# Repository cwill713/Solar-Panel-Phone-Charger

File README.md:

# Solar Smartphone Charger

This is the the project, assigned by [Dr. Rob Frohne](https://github.com/frohro), that [Joshua Mularczyk](https://github.com/JoshuaMularczyk) and I designed for our Power Electronics class. This project used our knowledge of power efficiency and stepping down voltage along with our knowledge of KiCAD and LTSpice to create our own portable solar phone charges. 

## Design Objectives:
- Output 5V from a higher input voltage
- Draw 1A at the output
- Inexpensive ($20-$30 Budget)
- AS efficient as possible

## Overview

Josh and I wanted to design a solar phone charger because we thought of the potential use of people who spend a lot of time outside. We also knew that Apple products need certain specifications to charge as oppose to Andriod products so we set out to figure out how to make our charger work for both.

The first simulation/schematic of our project allowed us to get the desired outputs, but we found that it was not very efficient, so we decided to redesign our board and end up with a new string of designs

The heart of our circuit is the [LM3478](https://www.ti.com/lit/ds/symlink/lm3478.pdf?HQS=dis-dk-null-digikeymode-dsf-pf-null-wwe&ts=1654180125781&ref_url=https%253A%252F%252Fwww.ti.com%252Fgeneral%252Fdocs%252Fsuppproductinfo.tsp%253FdistId%253D10%2526gotoUrl%253Dhttps%253A%252F%252Fwww.ti.com%252Flit%252Fgpn%252Flm3478) which is a high-efficiency low-side n-channel controller. This allows us to regulate any voltage between 2.39 and 40V that could come from our 10W solar panels

## Rev 7 Design

This is the most recent KiCad schematic for our circuit design. Josh used the Texas Instrument [Webench Power Designer](https://www.ti.com/design-resources/design-tools-simulation/webench-power-designer.html) to generate this step-down circuit. The design specified a 5V to 12V input voltage based on the likely solar panel outputs. We also specified the a maximum of 1A should be be able to be drawn from our circuit.

## Rev 7 Simulation

This is the complete simulation of our circuit. We can see here that at around 7ms, the output voltage of circuit is 5V

### Voltage Outputs (5V 2.7V 2V)

This is the simulation of the voltage dividers that shows the voltage going to our USB pins. V+, D+, and D-. This will be talked about more in the testing section.

### Input and Output Current

This simulations shows us that we achieved the low input voltage that we need. The 5 Ohm resistor allowed us to simulate the current our phone would draw from the circuit. The output current of 1A will allow us to power our phone with 5W.

## Rev 7 PCB Design

This is the PCB design of the board we sourced from [JLCPCB](https://jlcpcb.com/VGS?utm_source=gg_vgs&utm_medium=cpc&gclid=Cj0KCQjwqPGUBhDwARIsANNwjV4Y9aU908uwwHsgXCAJ3L9PZ44l-hPgCvsU4kgto-ll1H0iRJroh1UaAsKwEALw_wcB),

## Rev 6 Testing

Josh and I each constructed a our own boards and tested them. When testing the boards with a 0-18V 1A power supply, we found that the boards could charge Ti-84 calculators and Andriod phones, but not an iPhone. To see if we couldn't draw enough current from the power supply, we connected our board to 24V 3A power supply and saw the same results. After we performed some research, Josh found that we needed voltage across the D+ and D- pins, 2.7 and 2V respectivly. To achieve this, we created a votalde dividers using through-hole resistors and soldered them to the back of the boards. We then tested the boards and found that we were able to succesfully charge our iPhones.

After we tested the boards in the lab, we connected our boards to our solar panels and tested them outside. We found that we were getting around 4.8V and .96A at the output which gave us 4.61W at the output. 

## Rev 6 Results
The image on the left shows the voltage being supplied to the iPhone through the 24V 4A power suplies. The image on the right shows the current being drawn by the iPhone.

More images are avaialble in the [pictures](https://github.com/cwill713/Solar-Panel-Phone-Charger/tree/main/Pictures) folder. The video of testing made by Josh is availabel [here](https://youtu.be/SS7m2UqrDPg).

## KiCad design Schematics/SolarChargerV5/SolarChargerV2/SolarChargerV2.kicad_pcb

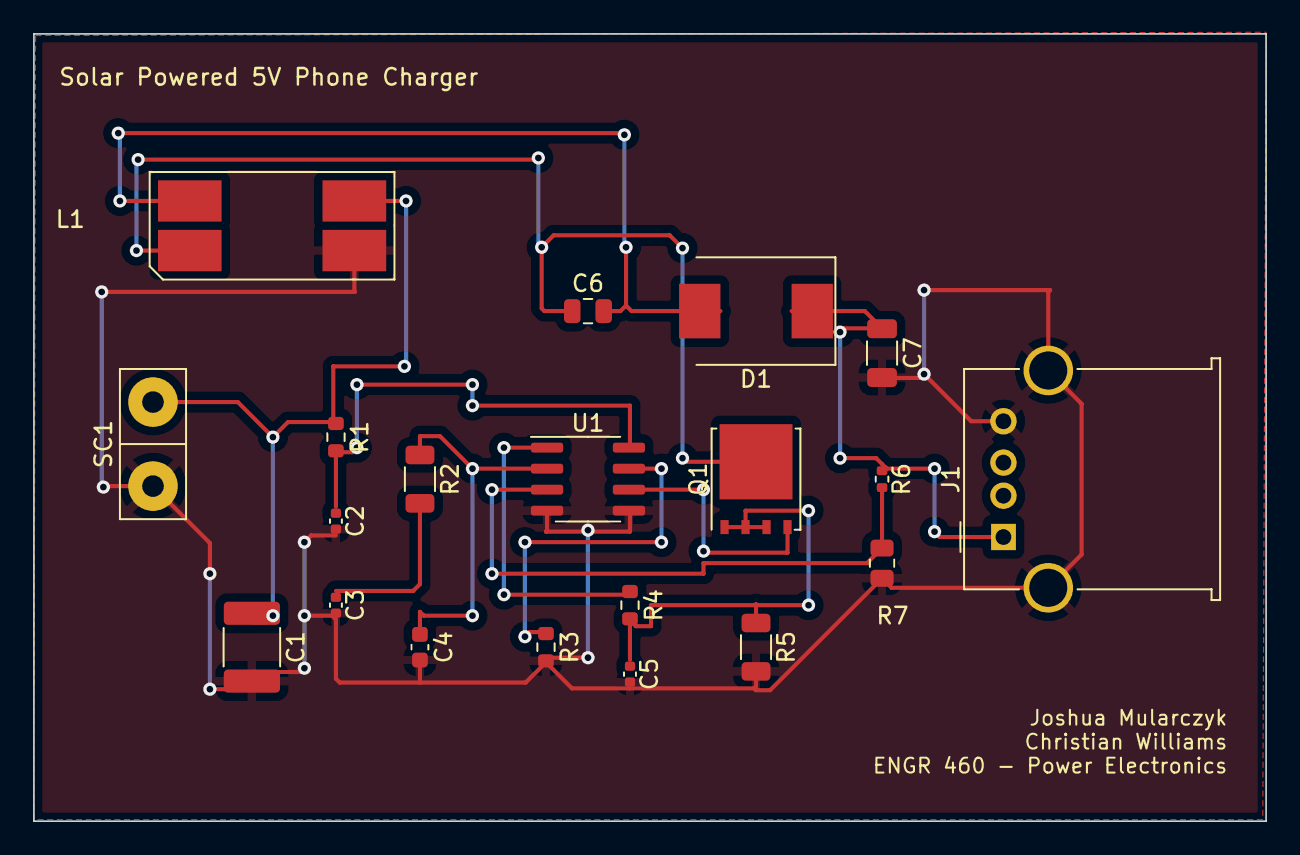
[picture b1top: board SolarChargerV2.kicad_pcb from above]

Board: 2 copper layers, 74.5 x 47.6 mm, 20 parts (0 on the bottom side), 13 nets.

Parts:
C1: 10u; C_1812_4532Metric
C2: 100n; C_0402_1005Metric
C3: 82n; C_0402_1005Metric
C4: 200p; C_0603_1608Metric
C5: 1n; C_0402_1005Metric
C6: 1u; C_0805_2012Metric
C7: 47u; C_1206_3216Metric
D1: B340; D_SMC
J1: USB_A; USB_A_Molex_67643_Horizontal
L1: 10u; DRQ
Q1: CSD16410Q5A; TDSON-8-1
R1: 20; R_0603_1608Metric
R2: 887; R_1206_3216Metric
R3: 51.1k; R_0603_1608Metric
R4: 100; R_0603_1608Metric
R5: 25m; R_1206_3216Metric
R6: 29.4k; R_0402_1005Metric
R7: 10k; R_0805_2012Metric
SC1: Solar_Cell; SIP-2
U1: LM3478MA_NOPB; SOIC-8_3.9x4.9mm_P1.27mm

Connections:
GND: C1.2, C2.2, C3.2, C4.2, C5.2, C7.2, J1.4 (GND), J1.5 (Shield), L1.4, R3.2, R5.2, R7.2, SC1.2 (-), U1.4 (AGND), U1.5 (PGND)
unnamed: C1.1, L1.3, R1.1, SC1.1 (+)
unnamed: C2.1, R1.2, U1.8 (VIN)
unnamed: C3.1, R2.2
unnamed: C4.1, R2.1, U1.2 (COMP)
unnamed: C5.1, Q1.1 (S), Q1.2 (S), Q1.3 (S), R4.2, R5.1
unnamed: C6.2, D1.2 (A), L1.2
unnamed: C7.1, D1.1 (K), J1.1 (VBUS), R6.1
unnamed: C6.1, L1.1, Q1.5 (D)
unnamed: R3.1, U1.7 (FA/SD)
unnamed: R4.1, U1.1 (ISEN)
unnamed: R6.2, R7.1, U1.3 (FB)
unnamed: Q1.4 (G), U1.6 (DR)

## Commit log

2022-06-06 Copied Files from Partner's Github
2022-06-08 no message
